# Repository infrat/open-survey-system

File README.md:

# Open Survey System (OSS)

**Open, affordable GNSS RTK platform** that enables centimeter‑level positioning (~10 mm XY / ~50 mm Z) using commodity, readily available modules. OSS aims to democratize survey‑grade measurements by publishing open hardware, firmware, and reference configurations.

> **Status:** early draft - architecture overview only. Detailed BOMs, Gerbers, STLs, and configuration guides will be added later.

---

## 1) System Overview

OSS consists of two building blocks:

1. **RTK Rover** - a portable GNSS receiver that works with common mobile apps (e.g., SW Maps, Locus GIS, QField, SurPad, LandStar etc.). The rover receives RTK corrections via NTRIP over the Internet **or** from a local Wi‑Fi NTRIP caster.
2. **Extension Kit (LoRa)** - a radio bridge that carries RTK corrections over longer distances using LoRa (433 MHz), (eg. when local access to RTK corrections over LTE is not available):
   - **LTE/LoRa Gateway** - fetches RTK corrections from an online NTRIP service (e.g., a national CORS) or from a local RTK base, then transmits them via LoRa.
   - **LoRa/Wi‑Fi Gateway** - receives LoRa packets with RTCM and exposes a local NTRIP caster over a Wi‑Fi Access Point.
   - **Local RTK Base Station** _(optional)_ - provides local corrections based on its precisely known position (surveyed once or derived from long averaging).

---

## 2) High‑Level Architectures (Topologies)

### A) Internet‑only (no radio) - rover is used in an area with internet access to RTK corrections (eg. by LTE)

### B) Radio‑relayed corrections (LoRa 433 MHz) - radio relay deployed in an area without internet access to RTK corrections network; corrections are calculated locally

### C) Hybrid (online source → local radio) - radio relay deployed in an area with internet access to RTK corrections network (over LTE/Starlink, etc.)

---

## 3) Component Roles

### RTK Rover

A compact, dual‑frequency GNSS RTK receiver that pairs with a mobile app. The app supplies RTK corrections (via Internet or a local NTRIP caster), while the rover provides position output to the app. Connectivity is kept simple (Bluetooth to the phone); no onboard Wi‑Fi or general‑purpose MCU is planned in the rover.

#### Enclosure

|                                    |                                    |
| ---------------------------------- | ---------------------------------- |
|  |  |
|  |  |

#### Inside

|                               |                               |
| ----------------------------- | ----------------------------- |
|  |  |

#### Outside

|                                 |                                 |
| ------------------------------- | ------------------------------- |
|  |  |

### LTE/LoRa Gateway (optional)

- Acts as an **NTRIP client** toward an online caster (e.g., CORS) **or** a local base station.
- **Encapsulates RTCM** and transmits over **LoRa 433 MHz (P2P)** to the LoRa/Wi‑Fi Gateway.

#### Photo

### LoRa/Wi‑Fi Gateway (optional)

- Receives **LoRa** packets and **reassembles RTCM** stream.
- Hosts a **local NTRIP caster** behind a Wi‑Fi **Access Point** for the rover/mobile app.

#### Photo

### Local RTK Base Station (optional)

- Provides **local RTCM** corrections from a fixed, accurately known position.
- Integrates with the LTE/LoRa Gateway to feed the radio uplink.

---

## 4) Data & Interfaces

- **Corrections:** RTCM 3.x over NTRIP (TCP/HTTP Basic).
- **Rover ↔ Phone link:** **Bluetooth SPP** (UART over BT using BT module, or BLE using ESP32).
- **Position output:** NMEA from rover to mobile apps.
- **Radio link:** LoRa 433 MHz, P2P mode (not LoRaWAN), optimized for low‑latency streaming.
- **Transport paths:**
  - Internet path: Mobile App (NTRIP client) → Online NTRIP Service → RTCM → **Bluetooth SPP** → Rover.
  - Radio path: Base or Online Service → LTE/LoRa Gateway → LoRa → LoRa/Wi‑Fi Gateway (NTRIP caster) → Mobile App → **Bluetooth SPP** → Rover.

---

## 5) Design Principles

- **Open & affordable:** publish hardware files (Gerbers), mechanical models (STL/STEP), firmware and configs.
- **Modular:** rover can operate standalone (Internet) or with the radio Extension Kit.
  > Extension Kit could be potentially used as a correction source to rovers from other manufacturers!
- **Interoperable:** works with mainstream mobile GIS apps.
- **Region‑aware:** radio operation must comply with local regulations (e.g., 433/869 MHz in EU).

---

## 6) Documentation

Component firmware and the shared, over-the-air specs are documented under `firmware/`:

### Shared specs (transmitter ↔ receiver)

The LoRa link is a contract between the two gateways, so its specs live in one canonical place — `firmware/shared/docs/` — and both firmwares must stay byte-compatible with them:

- [LoRa protocol](firmware/shared/docs/lora-protocol.md) - over-the-air packet format, fragmentation, radio parameters
- [Maintenance frame](firmware/shared/docs/maintenance-frame.md) - telemetry/maintenance and remote-command frames

### Transmitter (LTE/LoRa Gateway)

- [README](firmware/transmitter/README.md) - overview, hardware, quick start
- [Web UI config structure](firmware/transmitter/docs/config-structure.md) - configuration model and REST API
- [AGENTS.md](firmware/transmitter/AGENTS.md) - coding standards and workflow

### Receiver (LoRa/Wi‑Fi Gateway)

- [Architecture](firmware/receiver/docs/architecture.md) - task/core structure
- [Configuration](firmware/receiver/docs/configuration.md) - pins, timing, constants
- [NTRIP server](firmware/receiver/docs/ntrip-server.md) - local caster protocol flow
- [AGENTS.md](firmware/receiver/AGENTS.md) - coding standards and workflow

### Rover

- [README](firmware/rover/README.md) - overview and configuration

---

## 7) License

- Hardware: CERN OHL‑S v2 _(TBD)_
- Firmware/Software: Apache‑2.0 or MIT _(TBD)_
- Docs: CC‑BY‑4.0 _(TBD)_

---

### Notes

- Names and modules are placeholders for open, commonly available components.
- Rover = **GNSS RTK module + classic Bluetooth SPP module over UART**. Mobile app bridges NTRIP↔RTCM.
- This README intentionally omits implementation details; it is a high‑level map for the project structure and data flows.

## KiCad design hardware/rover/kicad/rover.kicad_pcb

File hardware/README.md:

# OSS Hardware

Bill of Materials (BOM) and fabrication files for each building block of the
Open Survey System (OSS).

| Component                   | Role                                                   | BOM                                      |
| --------------------------- | ------------------------------------------------------ | ---------------------------------------- |
| [Rover](rover/)             | Portable GNSS RTK receiver (GNSS + BLE/SPP bridge)     | [rover/BOM.md](rover/BOM.md)             |
| [Transmitter](transmitter/) | LTE/LoRa Gateway — NTRIP client → LoRa 433 MHz uplink  | [transmitter/BOM.md](transmitter/BOM.md) |
| [Receiver](receiver/)       | LoRa/Wi‑Fi Gateway — LoRa 433 MHz → local NTRIP caster | [receiver/BOM.md](receiver/BOM.md)       |

## Notes on the BOMs

- **Rover** is a custom PCB. Its BOM is derived directly from the KiCad
  schematic in [`rover/kicad/rover.kicad_sch`](rover/kicad/rover.kicad_sch) and
  is the authoritative parts list. A machine-readable copy lives in
  [`rover/bom.csv`](rover/bom.csv).
- **Transmitter** and **Receiver** are built around commodity ESP32 + SX1276
  LoRa development boards (no custom PCB yet), so their BOMs list ready-made
  modules and the few external parts that complete the build.
- Prices are rough indications (USD) for low-volume hobby quantities and will
  vary by region and supplier. Treat them as planning estimates, not quotes.
- Region-aware radio note: 433 MHz operation must comply with local
  regulations (e.g. 433/869 MHz in the EU). Pick antennas/power accordingly.

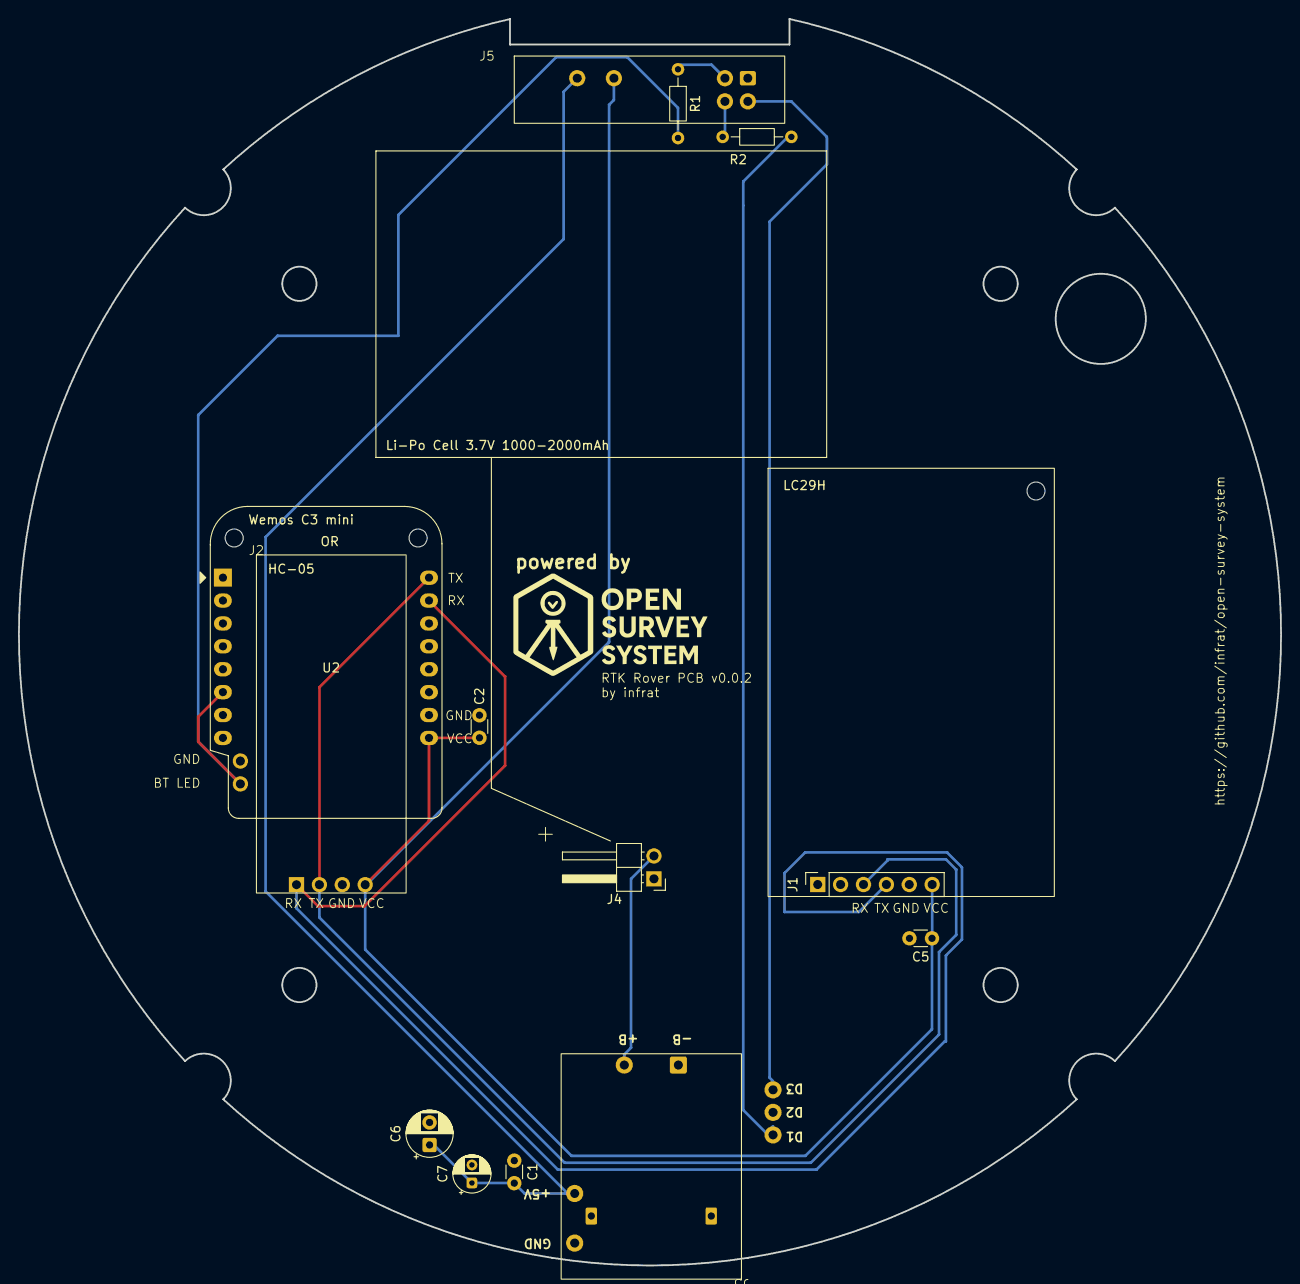
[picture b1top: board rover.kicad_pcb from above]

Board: 2 copper layers, 140.0 x 138.3 mm, 13 parts (0 on the bottom side), 11 nets.

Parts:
C1, C2, C5: 100n; C_Disc_D3.0mm_W1.6mm_P2.50mm
C6: 100uF; CP_Radial_D5.0mm_P2.50mm
C7: 10uF; CP_Radial_D4.0mm_P2.00mm
J1: LC29HDA_Socket; LC29H
J2: HC05_Socket; HC05
J3: BMS_Socket; BMS_FM5324
J4: BATT_Socket; PinHeader_1x02_P2.54mm_Horizontal
J5: CP_Socket; RTK_ControlPanel
R1, R2: 300R; R_Axial_DIN0204_L3.6mm_D1.6mm_P7.62mm_Horizontal
U2: WEMOS_C3_mini

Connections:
/+5V: C1.1, C6.1, C7.1, J3.4, J5.5
/+5V_SW: C2.1, C5.1, J1.6, J2.4, J5.6, U2.9 (VBus)
/+BAT: J3.2, J4.2
/BT_LED+: J5.2, R1.1
/GNSS_RX: J1.3, J2.2, U2.16 (TX)
/GNSS_TX: J1.4, J2.1, U2.15 (RX)
/PWR_LED+: J5.4, R2.1
/PWR_LED-: J3.5, J5.3
GND: C1.2, C2.2, C5.2, C6.2, C7.2, J1.5, J2.3, J2.6, J3.1, J3.3, J4.1, J5.1, U2.10 (GND)
unnamed: J2.5, R1.2, U2.6 (D4)
unnamed: J3.7, R2.2

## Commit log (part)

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2026-05-27 Initial commit: monorepo structure with receiver, transmitter, rover firmware and hardware
2026-06-19 Restructure into monorepo: firmware (receiver/transmitter), hardware, scripts
2026-06-19 Add .gitkeep to preserve empty hardware/receiver and hardware/transmitter dirs
2026-06-19 some translations + BOMs
